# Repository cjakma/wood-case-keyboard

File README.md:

![look0][look0]
![look1][look1]
![look2][look2]

# Brief
This is a hobby project, to make a copy of HHKB made of wood,
but not limited to it. It is fully customizable, parameterized
toolchain to generate a keyboard case.

## Features
- Made of wood
- Nice curved shape
- Customizable layout and shape (compatible with <http://www.keyboard-layout-editor.com/>)
- Open bottom (it minimizes overall height and you can show off your beautiful PCB!)
- Compatible with most PCBs built with SMD components(?)

## BOM
| Name                      | Quantities | Price     | Note                                                             |
| ------------------------- | ---------- | -----     | ---                                                              |
| 36x130x330mm walnut block | 1          | 2,080 JPY | <http://shop.woodworks-marutoku.com/products/muku/item/m003.php> |
| Cherry mx brown switches  | 60         | 4,640 JPY |                                                                  |
| PCB                       | 1          | 2,908 JPY | DIY <https://github.com/jinhwanlazy/hhkb-pcb>                    |
| Keycaps                   | 1          | 50 USD    | Special order from <http://www.maxkeyboard.com/>                 |

# Dependancies
- python3
- [python-shapely](https://pypi.python.org/pypi/Shapely)
- [Openscad](http://www.openscad.org/) - nightly version is recommended
- [OskarLinde/scad-utils](https://github.com/OskarLinde/scad-utils)
- [openscad/list-comprehension-demos](https://github.com/openscad/list-comprehension-demos)

# Build
Open `model/common.sacd` and modify parameters. You have to set `block_size`
properly even if you don't want to change anything. See
[Customization](#customization) section for details.

Following command will generate all 3D and 2D models you need, in
`stl` and `dxf` format, under `out` directory. Once you excecute `make` 
successfuly, you can open `model/preview.scad` and see how it will look
like.

    git clone https://github.com/jinhwanlazy/wood-case-keyboard
    cd wood-case-keyboard
    make

In OSX, you have to specify full path of openscad.

    make SCAD=/Applications/OpenSCAD.app/Contents/MacOS/OpenSCAD

# Customization
## Layout
Layout definitions are located under `layout` directory. They are 
compatible with <http://www.keyboard-layout-editor.com/>. 
You can feed one of them like this.

    make clean
    make LAYOUT=layout/plank.layout

![layouts][layouts]

## Parameters
preparing...

# Instruction
I used a [Shapeoko1](https://www.shapeoko.com/shapeoko1.html) for milling
, and [PyCam](http://pycam.sourceforge.net/) to generate 
toolpaths. And it was painfull job.
I have spent a lot of time to properly calibrate machine but
still encountered number of hardware problems(slipping bits, burning wood, missing steps, etc). 
I had to manually edit gcodes generated by PyCam. sometimes I forgot to do it,
and it came back with disasters. Most of them are covered with sanding process,
but some were unreversible, especially, you can see a hole at bottom right corner of the
case in the first picture.
I had to make monkeypatchs everytime something goes wrong. 
I highly recommend you to use commercial grade toolchain or just talk with manufacturer. 
I'll leave here very brief steps I have followed, rather than full instruction. 

0. I started with 330x130x34mm walnut block.
1. Print `back_holder.stl` and `tilt_holder.stl` with 3D printer.
2. Fix wood block on CNC mill, and carve it with `base.stl`. I had to split it
two pieces, due to limitaion of build space. 
![ins2][ins2]
3. Fix a pair of `tilt_holder` with screw at bottom of the wood block.
![ins3][ins3]
4. Place wood block again, and cut it with `top_cutout.dxf`.
Cut depth is `lip_depth`mm from the highest point of the woodblock. It is
defined in `common.scad`.
The size of the model is arbitrary. Ignore the contour.
You have to cutout only pockets of the model.
The origin of the model is set to bottom leftmost key position.
![ins4][ins4]
5. Cut with `plate.dxf`. Again, ignore contour, cutout pockets. Cut down 6mm
   from the surface of previous cut.
![ins5][ins5]
6. Take off the block and fix it with `back_holder`, then cut it with
   `bottom_cutout.dxf`. Cut down until the thickness of top becomes 5mm.
![ins6][ins6]
![ins7][ins7]
7. Take off the result. 
8. Make a hole at back, so that USB connector can show up.
   I did it by hand with dremel.
![ins8][ins8]
9. Sand and finish it with oil stain and varnish.

## Caveats
- The bottom surface is not flat. I started with flat wood block, but
  it distorted itself while milling.
- Open bottom may not a good idea in a long term. You always have to worry
  about conductive things on your desk.
- Layout support is quite limited at this point. It can parse only subset of
  [keyboard-layout-editor](http://www.keyboard-layout-editor.com/)'s syntax.
  Result maybe ugly with layouts other than 60% board.
- There seems to be errors in `base.stl` model. They are automatically fixed in most
  tools but it can be problametic in some cases. 
- You have to source PCB yourself unless you like [HHKB layout](https://github.com/jinhwanlazy/hhkb-pcb). 
- Note that the result on the pictures became smaller than 3D model.
  I had to cut it little more to hide my mistakes.
- There are some different types of [6u spacebar](https://deskthority.net/wiki/Space_bar_dimensions#6_units_.28114mm_wide.2C_3_keymounts.2C_57mm_and_38mm_apart.29).
  I hardcoded one of them in `model/plate.scad`. You have to manually modify it
  if you want something else.

[look0]: https://github.com/jinhwanlazy/wood-case-keyboard/raw/master/pics/IMG_2556.JPG "look0"
[look1]: https://github.com/jinhwanlazy/wood-case-keyboard/raw/master/pics/IMG_2566.JPG "look1"
[look2]: https://github.com/jinhwanlazy/wood-case-keyboard/raw/master/pics/IMG_2569.JPG "look2"
[ins2]: https://github.com/jinhwanlazy/wood-case-keyboard/raw/master/pics/IMG_2502.JPG "ins2"
[ins3]: https://github.com/jinhwanlazy/wood-case-keyboard/raw/master/pics/IMG_2507.JPG "ins3"
[ins4]: https://github.com/jinhwanlazy/wood-case-keyboard/raw/master/pics/IMG_2511.JPG "ins4"
[ins5]: https://github.com/jinhwanlazy/wood-case-keyboard/raw/master/pics/IMG_2514.JPG "ins5"
[ins6]: https://github.com/jinhwanlazy/wood-case-keyboard/raw/master/pics/IMG_2518.JPG "ins6"
[ins7]: https://github.com/jinhwanlazy/wood-case-keyboard/raw/master/pics/IMG_2519.JPG "ins7"
[ins8]: https://github.com/jinhwanlazy/wood-case-keyboard/raw/master/pics/IMG_2571.JPG "ins8"
[layouts]: https://github.com/jinhwanlazy/wood-case-keyboard/raw/master/pics/layouts.png "layouts"

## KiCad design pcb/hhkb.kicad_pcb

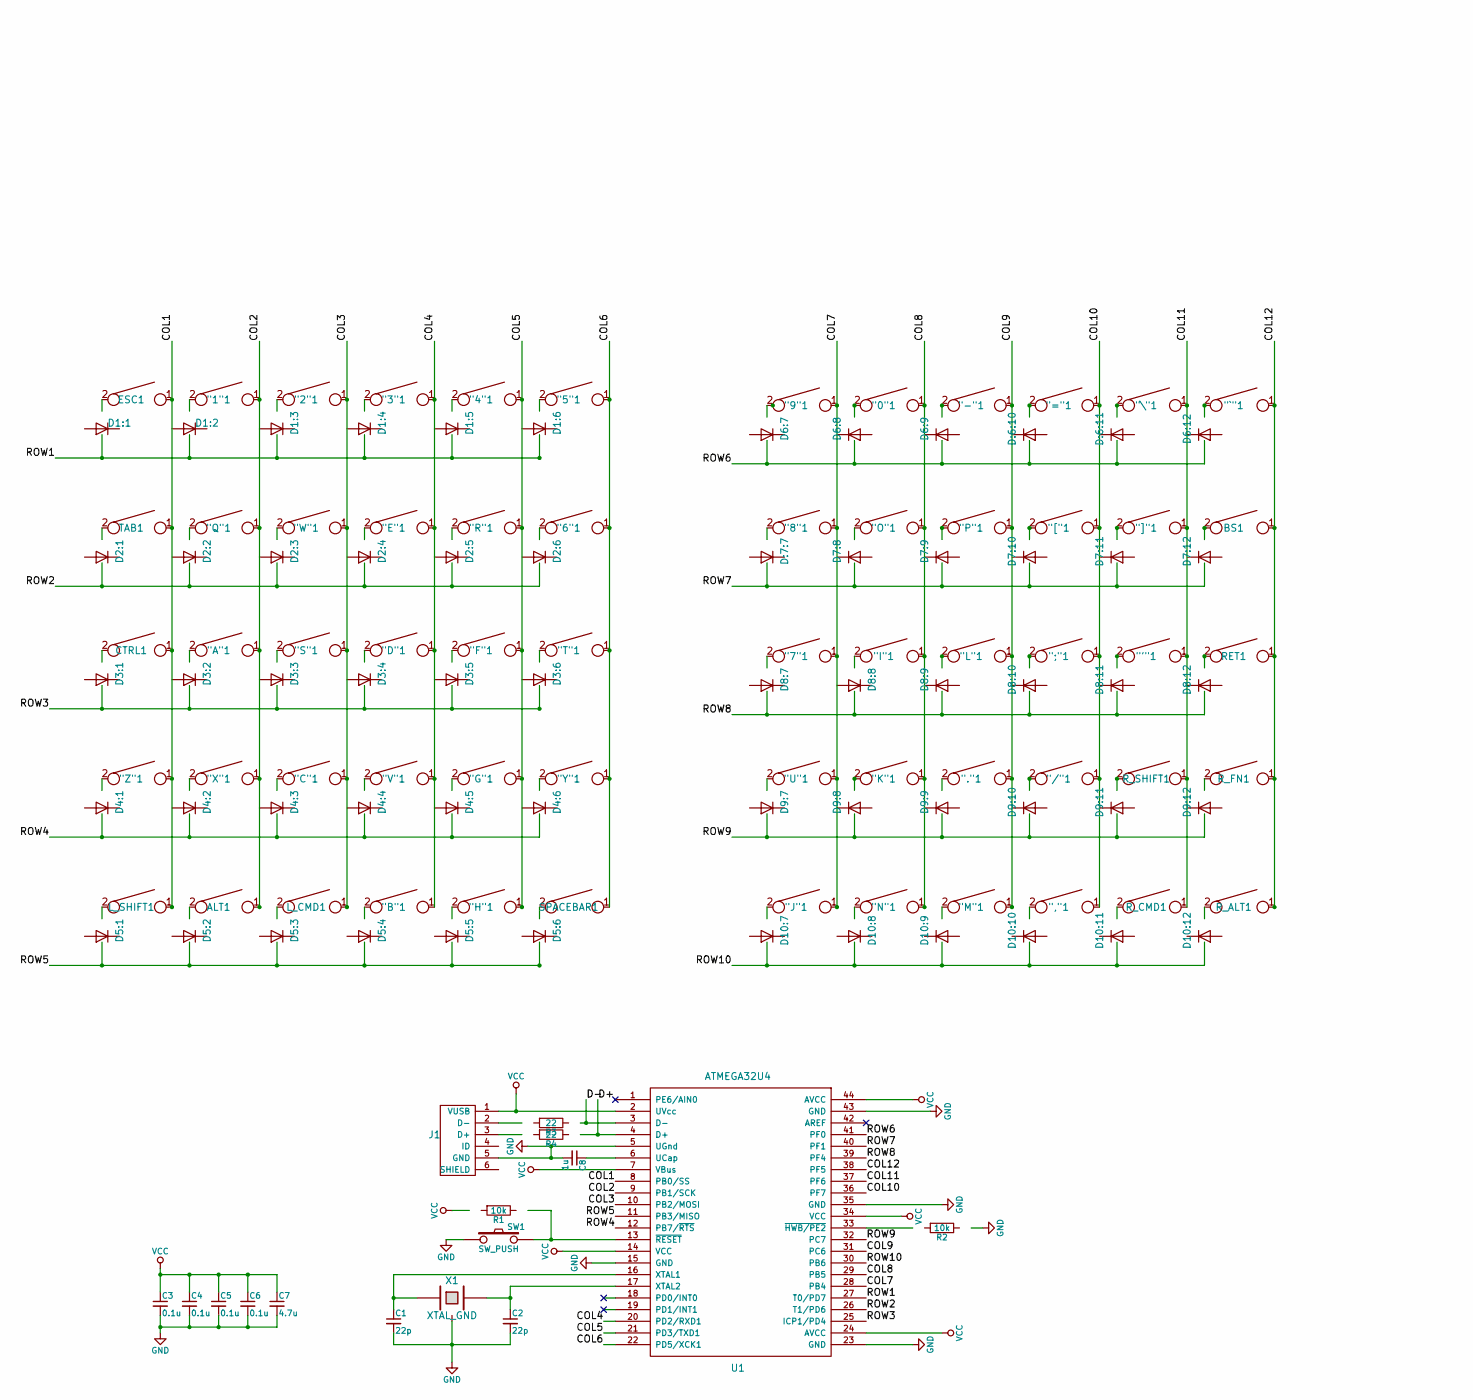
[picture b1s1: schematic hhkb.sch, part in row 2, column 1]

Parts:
"0"1, "1"1, "2"1, "3"1, "4"1, "5"1, "6"1, "7"1, "8"1, "9"1, "."1: KEYSW; MX_Plate_100H
"'"1: KEYSW; MX_Plate_100H
","1: KEYSW; MX_Plate_100H
"-"1: KEYSW; MX_Plate_100H
"/"1: KEYSW; MX_Plate_100H
";"1: KEYSW; MX_Plate_100H
"="1: KEYSW; MX_Plate_100H
"A"1: KEYSW; MX_Plate_100H
"B"1: KEYSW; MX_Plate_100H
"C"1: KEYSW; MX_Plate_100H
"D"1: KEYSW; MX_Plate_100H
"E"1: KEYSW; MX_Plate_100H
"F"1: KEYSW; MX_Plate_100H
"G"1: KEYSW; MX_Plate_100H
"H"1: KEYSW; MX_Plate_100H
"I"1: KEYSW; MX_Plate_100H
"J"1: KEYSW; MX_Plate_100H
"K"1: KEYSW; MX_Plate_100H
"L"1: KEYSW; MX_Plate_100H
"M"1: KEYSW; MX_Plate_100H
"N"1: KEYSW; MX_Plate_100H
"O"1: KEYSW; MX_Plate_100H
"P"1: KEYSW; MX_Plate_100H
"Q"1: KEYSW; MX_Plate_100H
"R"1: KEYSW; MX_Plate_100H
"S"1: KEYSW; MX_Plate_100H
"T"1: KEYSW; MX_Plate_100H
"U"1: KEYSW; MX_Plate_100H
"V"1: KEYSW; MX_Plate_100H
"W"1: KEYSW; MX_Plate_100H
"X"1: KEYSW; MX_Plate_100H
"Y"1: KEYSW; MX_Plate_100H
"Z"1: KEYSW; MX_Plate_100H
"["1: KEYSW; MX_Plate_100H
"\"1: KEYSW; MX_Plate_100H
"]"1: KEYSW; MX_Plate_100H
"`"1: KEYSW; MX_Plate_100H
ALT1: KEYSW; MX_Plate_100H
BS1: KEYSW; MX_Plate_150H
C1, C2: 22p; C_0805_HandSoldering
C3, C4, C5, C6: 0.1u; C_0805_HandSoldering
C7: 4.7u; C_0805_HandSoldering
C8: 1u; C_0805_HandSoldering
CTRL1: KEYSW; MX_Plate_175H
D1:1, D1:2, D1:3, D1:4, D1:5, D1:6, D2:1, D2:2, D2:3, D2:4, D2:5, D2:6, D3:1, D3:2, D3:3, D3:4, D3:5, D3:6, D4:1, D4:2, D4:3, D4:4, D4:5, D4:6, D5:1, D5:2, D5:3, D5:4, D5:5, D5:6, D6:7, D6:8, D6:9, D6:12, D7:8, D7:9, D7:10, D7:11, D7:12, D8:7, D8:8, D8:9, D8:10, D8:11, D8:12, D9:7, D9:8, D9:9, D9:10, D9:11, D9:12, D10:7, D10:8, D10:9, D10:10, D10:11, D10:12: D; D_SOD-123
D:6:10, D:6:11, D:7:7: D; D_SOD-123
ESC1: KEYSW; MX_Plate_100H
J1: USB_mini_micro_B; USB_miniB_hirose_5ST_hand
L_CMD1: KEYSW; MX_Plate_100H
L_SHIFT1: KEYSW; MX_Plate_225H
R1, R2: 10k; R_0805_HandSoldering
R3, R4: 22; R_0805_HandSoldering
RET1: KEYSW; MX_Plate_225H
R_ALT1: KEYSW; MX_Plate_100H
R_CMD1: KEYSW; MX_Plate_150H
R_FN1: KEYSW; MX_Plate_100H
R_SHIFT1: KEYSW; MX_Plate_175H
SPACEBAR1: KEYSW; MX_Plate_600H_Stepped
SW1: SW_PUSH; SW_SPST_TL3342
TAB1: KEYSW; MX_Plate_150H
U1: ATMEGA32U4; TQFP-44_10x10mm_Pitch0.8mm
X1: XTAL_GND; FA-238

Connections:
/COL1: "Z"1.1, CTRL1.1, ESC1.1, L_SHIFT1.1, TAB1.1, U1.8 (PB0/SS)
/COL2: "1"1.1, "A"1.1, "Q"1.1, "X"1.1, ALT1.1, U1.9 (PB1/SCK)
/COL3: "2"1.1, "C"1.1, "S"1.1, "W"1.1, L_CMD1.1, U1.10 (PB2/MOSI)
/COL4: "3"1.1, "B"1.1, "D"1.1, "E"1.1, "V"1.1, U1.20 (PD2/RXD1)
/COL5: "4"1.1, "F"1.1, "G"1.1, "H"1.1, "R"1.1, U1.21 (PD3/TXD1)
/COL6: "5"1.1, "6"1.1, "T"1.1, "Y"1.1, SPACEBAR1.1, U1.22 (PD5/XCK1)
/COL7: "7"1.1, "8"1.1, "9"1.1, "J"1.1, "U"1.1, U1.28 (PB4)
/COL8: "0"1.1, "I"1.1, "K"1.1, "N"1.1, "O"1.1, U1.29 (PB5)
/COL9: "-"1.1, "."1.1, "L"1.1, "M"1.1, "P"1.1, U1.31 (PC6)
/COL10: ","1.1, "/"1.1, ";"1.1, "="1.1, "["1.1, U1.36 (PF7)
/COL11: "'"1.1, "\"1.1, "]"1.1, R_CMD1.1, R_SHIFT1.1, U1.37 (PF6)
/COL12: "`"1.1, BS1.1, RET1.1, R_ALT1.1, R_FN1.1, U1.38 (PF5)
/D+: R4.1, U1.4 (D+)
/D-: R3.1, U1.3 (D-)
/ROW1: D1:1.1 (K), D1:2.1 (K), D1:3.1 (K), D1:4.1 (K), D1:5.1 (K), D1:6.1 (K), U1.27 (T0/PD7)
/ROW2: D2:1.1 (K), D2:2.1 (K), D2:3.1 (K), D2:4.1 (K), D2:5.1 (K), D2:6.1 (K), U1.26 (T1/PD6)
/ROW3: D3:1.1 (K), D3:2.1 (K), D3:3.1 (K), D3:4.1 (K), D3:5.1 (K), D3:6.1 (K), U1.25 (ICP1/PD4)
/ROW4: D4:1.1 (K), D4:2.1 (K), D4:3.1 (K), D4:4.1 (K), D4:5.1 (K), D4:6.1 (K), U1.12 (PB7/~RTS)
/ROW5: D5:1.1 (K), D5:2.1 (K), D5:3.1 (K), D5:4.1 (K), D5:5.1 (K), D5:6.1 (K), U1.11 (PB3/MISO)
/ROW6: D6:7.1 (K), D6:8.1 (K), D6:9.1 (K), D6:12.1 (K), D:6:10.1 (K), D:6:11.1 (K), U1.41 (PF0)
/ROW7: D7:8.1 (K), D7:9.1 (K), D7:10.1 (K), D7:11.1 (K), D7:12.1 (K), D:7:7.1 (K), U1.40 (PF1)
/ROW8: D8:7.1 (K), D8:8.1 (K), D8:9.1 (K), D8:10.1 (K), D8:11.1 (K), D8:12.1 (K), U1.39 (PF4)
/ROW9: D9:7.1 (K), D9:8.1 (K), D9:9.1 (K), D9:10.1 (K), D9:11.1 (K), D9:12.1 (K), U1.32 (PC7)
/ROW10: D10:7.1 (K), D10:8.1 (K), D10:9.1 (K), D10:10.1 (K), D10:11.1 (K), D10:12.1 (K), U1.30 (PB6)
GND: C1.2, C2.2, C3.2, C4.2, C5.2, C6.2, C7.2, C8.2, J1.5 (GND), R2.1, SW1.1, U1.5 (UGnd), U1.15 (GND), U1.23 (GND), U1.35 (GND), U1.43 (GND), X1.3
unnamed: "0"1.2, D6:8.2 (A)
unnamed: "1"1.2, D1:2.2 (A)
unnamed: "2"1.2, D1:3.2 (A)
unnamed: "3"1.2, D1:4.2 (A)
unnamed: "4"1.2, D1:5.2 (A)
unnamed: "5"1.2, D1:6.2 (A)
unnamed: "6"1.2, D2:6.2 (A)
unnamed: "7"1.2, D8:7.2 (A)
unnamed: "8"1.2, D:7:7.2 (A)
unnamed: "9"1.2, D6:7.2 (A)
unnamed: "'"1.2, D8:11.2 (A)
unnamed: ","1.2, D10:10.2 (A)
unnamed: "-"1.2, D6:9.2 (A)
unnamed: "."1.2, D9:9.2 (A)
unnamed: "/"1.2, D9:10.2 (A)
unnamed: ";"1.2, D8:10.2 (A)
unnamed: "="1.2, D:6:10.2 (A)
unnamed: "A"1.2, D3:2.2 (A)
unnamed: "B"1.2, D5:4.2 (A)
unnamed: "C"1.2, D4:3.2 (A)
unnamed: "D"1.2, D3:4.2 (A)
unnamed: "E"1.2, D2:4.2 (A)
unnamed: "F"1.2, D3:5.2 (A)
unnamed: "G"1.2, D4:5.2 (A)
unnamed: "H"1.2, D5:5.2 (A)
unnamed: "I"1.2, D8:8.2 (A)
unnamed: "J"1.2, D10:7.2 (A)
unnamed: "K"1.2, D9:8.2 (A)
unnamed: "L"1.2, D8:9.2 (A)
unnamed: "M"1.2, D10:9.2 (A)
unnamed: "N"1.2, D10:8.2 (A)
unnamed: "O"1.2, D7:8.2 (A)
unnamed: "P"1.2, D7:9.2 (A)
unnamed: "Q"1.2, D2:2.2 (A)
unnamed: "R"1.2, D2:5.2 (A)
unnamed: "S"1.2, D3:3.2 (A)
unnamed: "T"1.2, D3:6.2 (A)
unnamed: "U"1.2, D9:7.2 (A)
unnamed: "V"1.2, D4:4.2 (A)
unnamed: "W"1.2, D2:3.2 (A)
unnamed: "X"1.2, D4:2.2 (A)
unnamed: "Y"1.2, D4:6.2 (A)
unnamed: "Z"1.2, D4:1.2 (A)
unnamed: "["1.2, D7:10.2 (A)
unnamed: "\"1.2, D:6:11.2 (A)
unnamed: "]"1.2, D7:11.2 (A)
unnamed: "`"1.2, D6:12.2 (A)
unnamed: ALT1.2, D5:2.2 (A)
unnamed: BS1.2, D7:12.2 (A)
unnamed: C1.1, U1.16 (XTAL1), X1.1
unnamed: C2.1, U1.17 (XTAL2), X1.2
unnamed: C8.1, U1.6 (UCap)
unnamed: CTRL1.2, D3:1.2 (A)
unnamed: D1:1.2 (A), ESC1.2
unnamed: D2:1.2 (A), TAB1.2
unnamed: D5:1.2 (A), L_SHIFT1.2
unnamed: D5:3.2 (A), L_CMD1.2
unnamed: D5:6.2 (A), SPACEBAR1.2
unnamed: D8:12.2 (A), RET1.2
unnamed: D9:11.2 (A), R_SHIFT1.2
unnamed: D9:12.2 (A), R_FN1.2
unnamed: D10:11.2 (A), R_CMD1.2
unnamed: D10:12.2 (A), R_ALT1.2
unnamed: J1.2 (D-), R3.2
unnamed: J1.3 (D+), R4.2
unnamed: R2.2, U1.33 (~HWB/PE2)
VCC: C3.1, C4.1, C5.1, C6.1, C7.1, J1.1 (VUSB), R1.2, U1.2 (UVcc), U1.7 (VBus), U1.14 (VCC), U1.24 (AVCC), U1.34 (VCC), U1.44 (AVCC)

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
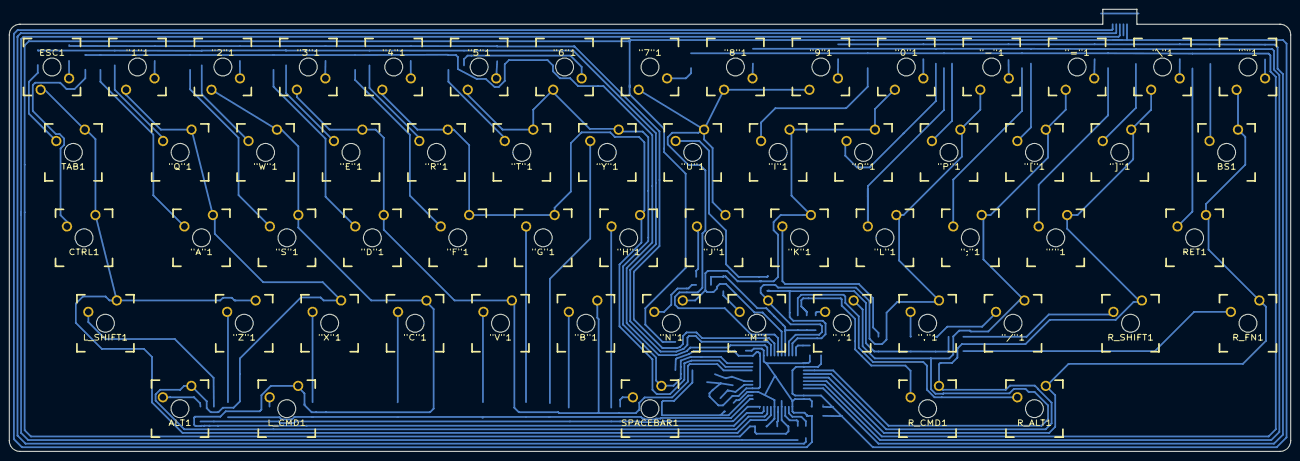
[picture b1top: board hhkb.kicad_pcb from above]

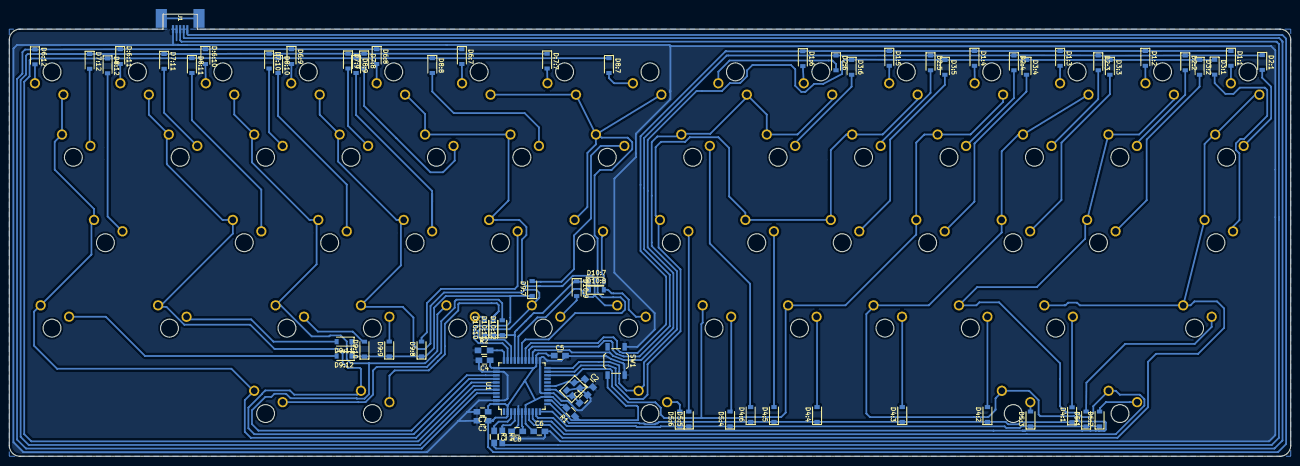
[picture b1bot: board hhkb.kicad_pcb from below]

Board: 2 copper layers, 285.8 x 98.6 mm, 136 parts (76 on the bottom side), 93 nets.

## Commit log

2017-02-16 initial commit; Outer shape of case is done
2017-02-20 add hhkb layout with all modifier size 150
2017-02-20 add keycap preview
2017-02-20 add pcb modules
2017-02-20 some more keycaps
2017-02-20 round cutout
2017-02-22 add kicad lib
2017-02-22 pcb is almost done
2017-02-22 hhkb layout with 4u spacebar
2017-02-22 add gerber files
2017-02-22 add pcb2gcode conf
2017-02-22 ignore img and dxf
2017-02-22 update gitignore
2017-02-22 add BOM, work in progress
2017-02-22 files updated
2017-02-22 drop voronoi
2017-02-22 use jumper to represent jumper, rather than 0ohm resister
2017-02-22 add readme
2017-03-01 add stl files
2017-03-08 Lots of changes
    add instructions in readme
    rm keycaps preview
    rm legacy stl
    separate scad files for each toolpath
    update gitignore
2017-03-08 update readme; make room for pcb
2017-03-08 remove dupe
2017-03-08 add procedure
2017-03-08 add some placeholder procedures
2017-03-08 add splitted shape
2017-03-08 naive makefile
2017-03-08 find OpenSCAD installed by brew
2017-03-08 add stl and gcodes
2017-03-08 sane offsets
2017-03-08 adjust offsets
2017-03-08 fix collision
2017-03-08 boundary inside
2017-03-08 update doc to match measurement
2017-03-08 regenerate gcodes
2017-03-08 add pcb gcodes
2017-03-10 more configures
2017-03-10 avoid corner collision
2017-03-10 add tilt holder
2017-03-10 cut lip and slots same time
2017-03-11 add cutout margin
2017-03-11 rename shape to base, better positioning
2017-03-18 untrack stls
2017-03-18 ignore kicad tmp files
2017-03-18 stop using pcb2gcode
2017-03-18 add back_holder
2017-03-18 rework pcb artwork
2017-03-18 rm legacy; 4u spacebar pcb
2017-03-18 enlarge trace width
2017-03-19 redraw outline
2017-03-26 fix left super size
2017-03-27 optimize some path
2017-03-27 add minimal firmware conf
2017-03-28 export pcb to separate repo
2017-03-29 mv firmware to pcb repo
2017-04-05 clean unused submodule
2017-04-05 clean code
2017-04-05 clean dependancies
2017-04-05 import dome layouts from keyboard-layout-editor
2017-04-05 fix preview
2017-04-05 add pictures
2017-04-05 rotate pics
2017-04-05 add a image
2017-04-05 no full path
2017-04-05 more pics in readme
2017-04-05 fix english
2017-04-05 add caveats
2017-04-06 add more pics
2017-04-07 build prewview also
2017-04-07 rot direction was wrong
2017-04-07 fix stabilizer dimension
2017-04-07 some more layouts
2017-04-07 typo
2017-04-07 fix bug with vertically long switches
2017-04-07 caveats at the bottom
2017-04-07 add layout comparison img
2017-04-07 add layout comparison img on readme
2017-04-07 add spacebar dimension explanation
2017-04-07 add usb connector picture
2017-04-08 add BOM
2017-04-09 change money symbol
